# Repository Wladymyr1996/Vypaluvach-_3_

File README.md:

# Vypaluvach-_3_
"Vypaluvach" this is my project of CNC image woodburner

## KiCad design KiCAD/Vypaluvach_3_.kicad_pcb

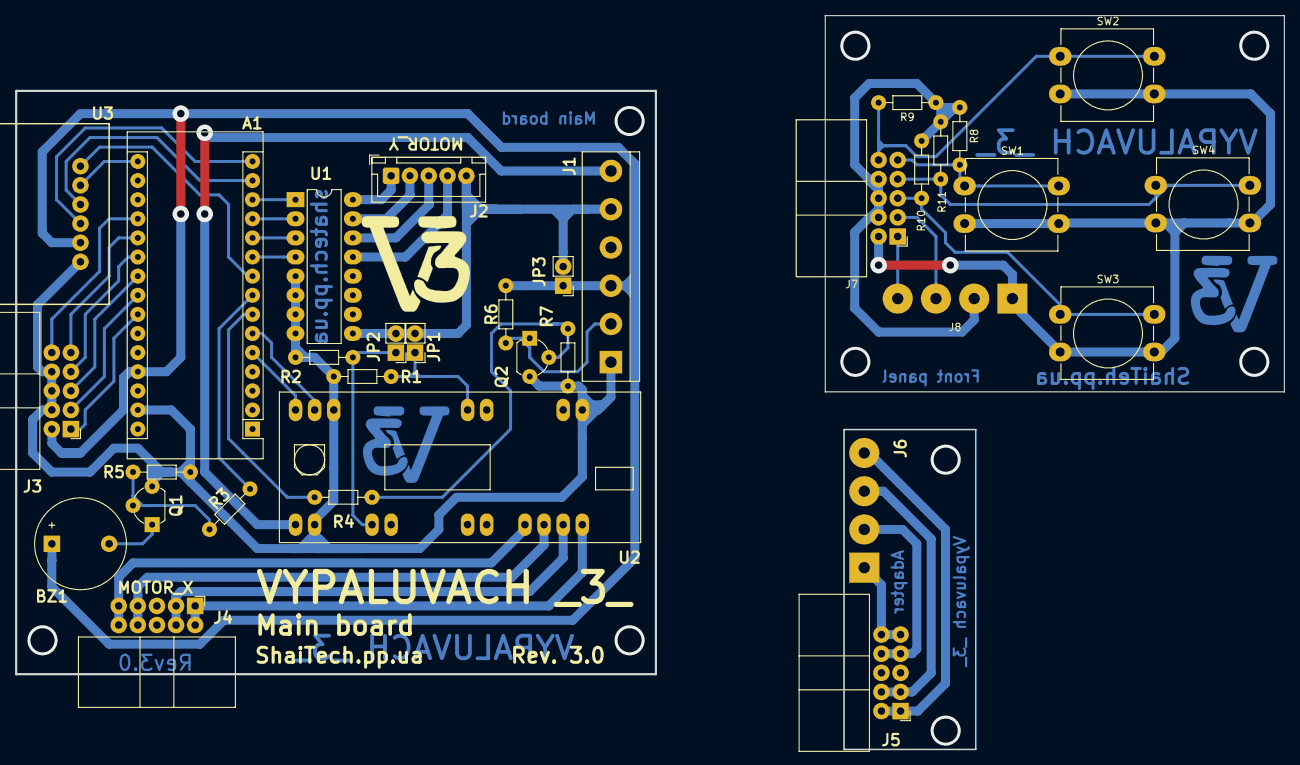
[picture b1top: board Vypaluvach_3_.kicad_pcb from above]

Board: 2 copper layers, 168.4 x 97.4 mm, 33 parts (0 on the bottom side), 48 nets.

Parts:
A1: Arduino_Nano_v3.x; Arduino_Nano
BZ1: Buzzer; Buzzer_12x9.5RM7.6
J1: POWER; TerminalBlock_bornier-6_P5.08mm
J2: OUT_Y; JST_XH_B05B-XH-A_1x05_P2.50mm_Vertical
J3, J7: PANEL; IDC-Header_2x05_P2.54mm_Horizontal
J4, J5: OUT_X; IDC-Header_2x05_P2.54mm_Horizontal
J6: Motor_Connector; SolderWirePad_1x04_P5.08mm_Drill1.5mm
J8: LCD_Connector; SolderWirePad_1x04_P5.08mm_Drill1.5mm
JP1: MS1; PinHeader_1x02_P2.54mm_Vertical
JP2: MS2; PinHeader_1x02_P2.54mm_Vertical
JP3: PWR_SEL; PinHeader_1x02_P2.54mm_Vertical
Q1, Q2: BC547; TO-92L_Wide
R1, R2, R5, R6, R7, R8, R9, R10, R11: 4.7K; R_Axial_DIN0204_L3.6mm_D1.6mm_P7.62mm_Horizontal
R3, R4: 2.2K; R_Axial_DIN0204_L3.6mm_D1.6mm_P7.62mm_Horizontal
SW1: BTN_BACK; SW_PUSH-12mm_Wuerth-430476085716
SW2: BTN_UP; SW_PUSH-12mm_Wuerth-430476085716
SW3: BTN_DOWN; SW_PUSH-12mm_Wuerth-430476085716
SW4: BTN_OK; SW_PUSH-12mm_Wuerth-430476085716
U1: ULN2003A; DIP-16_W7.62mm_LongPads
U2: EasyDriver
U3: MicroSDCardAdapter

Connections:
+5V: J1.5, J2.5, JP1.2, JP2.2, JP3.2, U1.9
+5VSB: A1.27, BZ1.1, J1.3, J3.2, JP3.1, R6.2, U3.5
+12V: J1.6, U2.8
/OtherPCB/ADPTR_OUT1_X: J5.9, J5.10, J6.1
/OtherPCB/ADPTR_OUT2_X: J5.7, J5.8, J6.2
/OtherPCB/ADPTR_OUT3_X: J5.3, J5.4, J6.3
/OtherPCB/ADPTR_OUT4_X: J5.1, J5.2, J6.4
/OtherPCB/PNL_5V: J7.2, J8.1, SW1.2, SW2.2, SW3.2, SW4.2
/OtherPCB/PNL_BTN_BACK: J7.9, R8.2, SW1.1
/OtherPCB/PNL_BTN_DOWN: J7.5, R10.2, SW3.1
/OtherPCB/PNL_BTN_OK: J7.7, R11.2, SW4.1
/OtherPCB/PNL_BTN_UP: J7.10, R9.2, SW2.1
/OtherPCB/PNL_GND: J7.4, J7.6, J7.8, J8.2, R8.1, R9.1, R10.1, R11.1
/OtherPCB/PNL_LCD_SCL: J7.1, J8.4
/OtherPCB/PNL_LCD_SDA: J7.3, J8.3
BTN_BACK: A1.20, J3.9
BTN_DOWN: A1.22, J3.5
BTN_OK: A1.21, J3.7
BTN_UP: A1.19, J3.10
BUZZER_CTRL: A1.8, R3.2
DIR_X: A1.5, U2.7
GNDD: A1.29, J1.1, J3.4, J3.6, J3.8, Q1.3, Q2.3, R1.1, R2.1, R5.1, R7.1, U1.5, U1.6, U1.7, U1.8, U2.1, U2.5, U2.9, U3.6
HEAD_ON: J1.2, Q2.1, R6.1
HEAD_ON_CTRL: A1.7, R4.2
IN1_Y: A1.13, U1.1
IN2_Y: A1.12, U1.2
IN3_Y: A1.11, U1.3
IN4_Y: A1.10, U1.4
LCD_SCL: A1.24, J3.1
LCD_SDA: A1.23, J3.3
MS1_X: JP1.1, R1.2, U2.4
MS2_X: JP2.1, R2.2, U2.10
unnamed: BZ1.2, Q1.1
unnamed: Q1.2, R3.1, R5.2
unnamed: Q2.2, R4.1, R7.2
OUT1_X: J4.1, J4.2, U2.17
OUT1_Y: J2.1, U1.16
OUT2_X: J4.3, J4.4, U2.16
OUT2_Y: J2.2, U1.15
OUT3_X: J4.7, J4.8, U2.15
OUT3_Y: J2.3, U1.14
OUT4_X: J4.9, J4.10, U2.14
OUT4_Y: J2.4, U1.13
SD_CS: A1.9, U3.1
SD_MISO: A1.15, U3.4
SD_MOSI: A1.14, U3.3
SD_SCK: A1.16, U3.2
STEP_X: A1.6, U2.6

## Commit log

2019-09-09 main commit
2022-06-20 Fix uncommited files
